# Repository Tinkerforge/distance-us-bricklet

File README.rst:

Distance US Bricklet
====================

This repository contains the firmware source code and the hardware design
files. The documentation generator configs can be found at
https://github.com/Tinkerforge/generators

Repository Content
------------------

software/:
 * examples/: Examples for all supported languages
 * build/: Compiled files
 * src/: Source code of firmware
 * Makefile: Makefile to build project

hardware/:
 * Contains KiCad project files and additionally schematics as PDF

datasheets/:
 * Contains datasheets for sensors and complex ICs that are used

Hardware
--------

The hardware is designed with the open source EDA Suite KiCad
(http://www.kicad.org). Before you are able to open the files,
you have to install the Tinkerforge kicad-libraries
(https://github.com/Tinkerforge/kicad-libraries). You can either clone
them directly in hardware/ or clone them in a separate folder and
symlink them into hardware/
(ln -s kicad_path/kicad-libraries project_path/hardware). After that you
can open the .pro file in hardware/ with KiCad and from there view and
modify the schematics and the PCB layout.

Software
--------

If you want to do your own Brick/Bricklet firmware development we highly
recommend that you use our build environment setup script and read the
tutorial (https://www.tinkerforge.com/en/doc/Tutorials/Tutorial_Build_Environment/Tutorial.html).

To compile the C code we recommend you to install the newest GNU Arm Embedded
Toolchain (https://launchpad.net/gcc-arm-embedded/+download).
You also need to install bricklib (https://github.com/Tinkerforge/bricklib)
and brickletlib (https://github.com/Tinkerforge/brickletlib).

You can either clone it directly in software/src/ or clone it in a
separate folder and symlink it into software/src/
(ln -s bricklib_path/bricklib project_path/software/src/ and
ln -s brickletlib_path/brickletlib project_path/software/src/).
Finally make sure to have CMake installed
(http://www.cmake.org/cmake/resources/software.html).

After that you can build the firmware by invoking make in software/.
The firmware (.bin) can then be found in software/build/ and uploaded
with brickv (click button "Flashing" on start screen).

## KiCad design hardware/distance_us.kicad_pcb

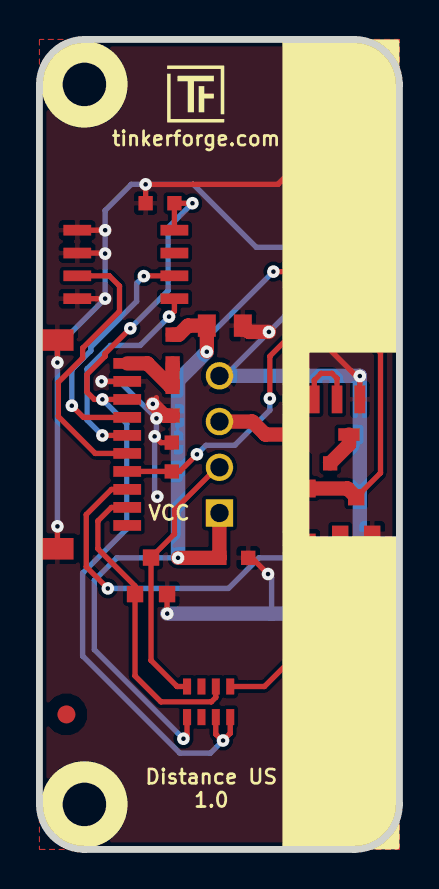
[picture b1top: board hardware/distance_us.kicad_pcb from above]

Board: 2 copper layers, 20.0 x 45.0 mm, 26 parts (0 on the bottom side), 15 nets.

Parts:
C1, C2, C4, C5, C7: 100nF; C0603
C3: 2.2uF 10V; C0805
C6: 0,1µF NP0; C1206
D1: BAS16H; SOD-123
Fiducial_Mark: VAL**; Fiducial_Mark
Fiducial_Mark#2: VAL**; Fiducial_Mark
L1: FB; C0603
P1: CON-SENSOR
P2: CONN_4; pin_array_4x1
P2#2: CONN_4; distanceUS_overlay
Q1, Q2: 2N7002P; SOT23GDS
R1: 160k; R0603
RP1: 10k; 0603X4
U1: LMV358LI; SOIC8
U2: M24C64; SOIC8
U3, U4, U5, U6: DRILL; DRILL_NP
VAL: WEEE_7mm
VAL#2: CE_5mm

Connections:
+5V: C1.2, L1.1, P1.1
GND: C1.1, C2.1, C3.2, C4.2, C5.1, C6.2, C7.1, P1.2, P1.EP, P2.4, Q1.S, Q2.S, U1.4, U2.1, U2.2, U2.4
unnamed: C5.2, P1.7, U1.6, U1.7
unnamed: C6.1, Q2.D, R1.1, U1.5
unnamed: D1.1, P2.3
unnamed: D1.2, R1.2
unnamed: P1.4, U2.6
unnamed: P1.5, U2.5
unnamed: P1.6, U2.3
unnamed: P1.8, Q2.G, RP1.1
unnamed: P1.9, Q1.G, RP1.2
unnamed: U1.2, U1.3
Trigger: P2.2, Q1.D, RP1.4
VAA: C2.2, C3.1, C7.2, L1.2, P2.1, RP1.5, U1.8
VCC: C4.1, P1.3, RP1.7, RP1.8, U2.8

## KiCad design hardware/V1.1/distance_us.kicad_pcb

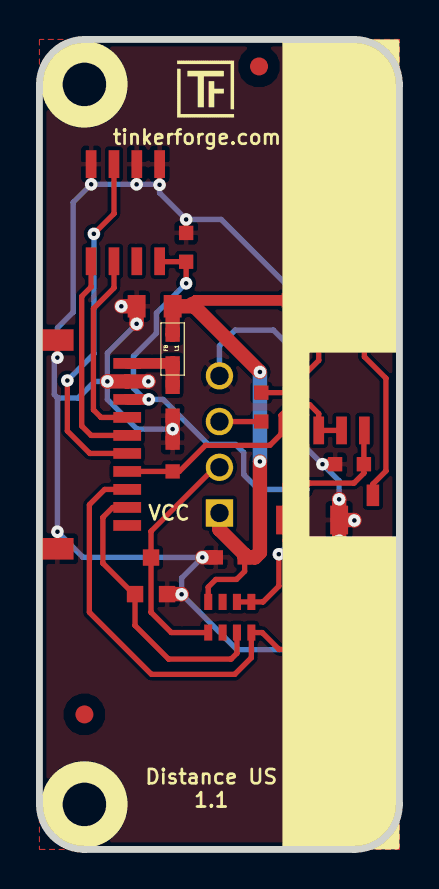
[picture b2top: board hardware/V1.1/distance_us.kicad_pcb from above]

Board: 2 copper layers, 20.0 x 45.0 mm, 29 parts (0 on the bottom side), 17 nets.

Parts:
C1, C3, C4, C5, C7: 100nF; C0603
C2: 2.2uF 10V; C0805
C6: 0,1µF NP0; C1206
D1: BAS16H; SOD-123
Fiducial_Mark: VAL**; Fiducial_Mark
Fiducial_Mark#2: VAL**; Fiducial_Mark
L1: FB; 0603
P1: CON-SENSOR
P2: CONN_4; pin_array_4x1
P2#2: CONN_4; distanceUS_overlay
Q1, Q2: 2N7002P; SOT23GDS
R1: 160k; R0603
R2, R3, R4: 10k; R0603
RP1: 10k; 0603X4
U1: M24C64; SOIC8
U2: LMV358LI; SOIC8
U3, U4, U5, U6: DRILL; DRILL_NP
VAL: CE_5mm
VAL#2: WEEE_7mm_back; WEEE_7mm

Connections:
+5V: C1.2, L1.1, P1.1
GND: C1.1, C2.2, C3.2, C4.1, C5.1, C6.2, C7.1, P1.2, P1.EP, P2.4, Q1.S, Q2.S, R3.1, U1.1, U1.2, U1.4, U2.4
unnamed: C5.2, P1.7, U2.6, U2.7
unnamed: C6.1, Q2.D, R1.1, U2.5
unnamed: D1.1, U2.1
unnamed: D1.2, R1.2
unnamed: P1.4, U1.6
unnamed: P1.5, U1.5
unnamed: P1.6, U1.3
unnamed: P1.8, Q2.G, RP1.4
unnamed: P1.9, Q1.G, RP1.3
unnamed: P2.3, R4.1
unnamed: R2.1, R3.2, U2.2
unnamed: R4.2, U2.3
Trigger: P2.2, Q1.D, RP1.1
VAA: C2.1, C7.2, L1.2, P2.1, R2.2, RP1.8
VCC: C3.1, C4.2, P1.3, RP1.5, RP1.6, U1.8, U2.8

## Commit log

2013-08-07 Initial commit of Distance US Bricklet plugin
2013-08-21 windows: Don't trigger a build in generate_makefile.bat
    Also use normal make instead of a special named one.
2013-09-16 Change Distance measurement according to latest hardware version
2013-09-16 Add Examples for Distance US Bricklet
2013-10-15 hardware check-in for distance us
2013-10-15 add license file
2013-10-18 Fix name to fit naming standard
2013-11-20 Change pins to correct version
2013-11-21 Remove unused state of state machine
2013-11-21 Try adding moving average, doesn't work yet
2013-11-21 Move averaging to the right place
2013-11-27 Adapt examples to API change
2013-12-19 Fix wrong length for GetDebounce packet (through brickletlib)
2014-01-06 Reorder elements in BrickContext to satisfy 256 byte size limit
2014-01-10 Add Perl examples
2014-01-15 php: Use const for constant values
2014-02-07 Add Mathematica examples
2014-02-10 perl: fixed namespace
2014-02-12 javascript: add examples
2014-02-18 javascript: examples fixed
2014-02-20 javascript: add html examples
2014-02-24 javascript: port 4280, startExample()
2014-02-28 javascript: Break long lines and cleanup whitespace
2014-03-05 Add LabVIEW examples
2014-03-06 labview: Add examples in LV2010 format
2014-03-27 matlab: add examples
2014-04-02 java: Unify constants style
2014-04-02 perl: Unify print style
2014-04-17 matlab: Adapt examples to new callback style
2014-04-17 matlab: Add parentheses to make pygments happy
2014-07-15 java: Replace System.console() usage with an Eclipse compatible pattern
2014-12-02 Use ReadLine instead of ReadKey for C# example
2015-02-13 vbnet: Use ReadLine instead of ReadKey
    Because ReadKey doesn't work with a pipe as stdin on the RED Brick.
2015-03-02 windows: Stop cmake from searching for mingw32-make.exe
    Using MinGW Makefiles as generator makes cmake search for mingw32-make.exe
    which might not be installed because GnuWin32's make.exe is used instead.
2015-03-26 update hardware files
2015-03-26 prototype data for new version
2015-04-09 c: Whitespace
2015-06-24 javascript: Clean up output creation
2015-06-24 vbnet: Fix typos
2015-07-23 Make JavaScript browser example textarea readonly
2015-07-27 Cleanup C/C++, C#, Java, Python and Ruby examples
2015-07-29 Reformat changelog
2015-08-07 Use full device class name in Python examples
2015-08-12 Fix minor warnings in C/C++ examples
2015-08-13 Use correct simple value type
2015-08-14 Fix threshold value type in Java example
2015-08-14 Cleanup Delphi examples
2015-08-18 Cleanup VB.NET examples
2015-08-19 Cleanup Perl examples
2015-08-21 Use shorter print statement in Perl example
2015-09-01 new prototype to remove 5V stability problems
2015-09-09 Duplicate cmake call to fix bug during cmake creation
2015-09-25 fiducials added, drc run
2015-09-25 fix fiducial settings
2015-09-30 Generator based example cleanup
2015-11-12 matlab: Fix callback handling for R2014a
    http://undocumentedmatlab.com/blog/matlab-callbacks-for-java-events-in-r2014a
2015-11-25 Include date and commit into changelog
2016-05-18 c: Add missing device destroy call
2016-07-01 Make the change UID comment more explicit
2016-07-01 Add missing moving average reinitialization on length change
    Also handle an initially incomplete history.
2016-07-15 Add changelog commit after the fact
2017-04-13 csharp: Adapt example
2017-04-21 shell: Adapt example
2017-06-02 octave: Use javaObject instead of deprecated java_new
2017-11-30 Update examples from generator
2017-12-07 mathematica: Also generate .nb files
2018-01-26 c: Fine-tune printf format
2018-02-19 javascript: Close div tag correctly
2018-02-20 Cleanup KiCad libraries config
    Ensure LibDir=kicad-libraries and LibName1=tinkerforge.
    Remove special library.
2018-03-27 Add 3d information (final)
2018-03-27 Add 3d files (*.FCStd & *.step)
2018-03-27 Fix schematic layout and symbols
2018-03-27 Add 3d models (*.FCstd & *.step)
2018-05-24 perl: Use strict in examples
2018-07-11 Add Makefile with docker support
2018-07-11 Update directory structure and build instructions
2018-07-11 Remove obsolete generate_makefile scripts
2018-09-14 vbnet: Fix typo in comment
2018-11-06 Add rust examples
2018-11-07 rust: Accept host names for ip connection, fix naming inconsistencies
2018-11-07 rust: Rename callback receivers.
2018-12-14 Add go examples.
2018-12-18 go: Change import path.
2018-12-18 go: Change import path again.
2018-12-20 rust: Reformat examples.
2019-01-24 mqtt: Add examples.
2019-01-24 mqtt: Fix example header.
2019-01-24 mqtt: Remove executable bit in example permissions.
2019-01-24 go: Minor example fixes.
2019-01-24 mqtt: Minor example fixes.
2019-03-28 mqtt: Fix whitespace.
2019-08-22 c: Adapt to bindings changes
2020-01-13 examples: Use python3 input instead of python2 raw_input.
2020-01-13 examples: mqtt: Remove trailing whitespace.
2020-04-14 mqtt: Fix device name format
2021-10-25 Update KiCad link
    https://www.kicad.org/blog/2021/10/Avoid-links-to-former-kicad-domain/
2022-05-10 go: Fix format string
2022-07-06 Add license files.

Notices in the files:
hardware/V1.1/distance_us.kicad_pcb:
Licensed under CERN OHL v.1.1
Copyright (©) 2015, B.Nordmeyer
Copyright Tinkerforge GmbH 2015.
This documentation describes Open Hardware and is licensed under the
CERN OHL v. 1.1.
hardware/distance_us.kicad_pcb:
Copyright (©) 2013, B.Nordmeyer
Copyright Tinkerforge GmbH 2013.
